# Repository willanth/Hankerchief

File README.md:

# Hankerchief

This is a microcontroller driven signal source, used to extend the operating frequencies of the VK3YNG foxhunt sniffer.

The main components of this system are:
* STM32 Nuleo32 board (I used the L432KC) 
* Silabs Si4464 transciever chip
* ADE-1 mixer
* 3.3VDC boost converter suppled by 2x AA/LR6 batteries

There are provisions for user controls (J8 battery on/off, J11 shift frequency) as well as making use of the IO on the Nucleo module that isn't tied up operating the signal source.  There is a provsion for a bicolor LED, and for external 5V power input through a micro-B USB port.
**_IMPORTANT NOTE_**:  
* There is no battery charging facility through the USB power connector
* There is no USB Data access to the Nucleo32 through the USB power connector
* 3.3V Power is supplied by the Nucleo32 onboard regulator (500mA max) when USB power is connected
* The Nucleo32 is not configured for 5V supply and 3.3V source out of the box, it requires a simple modification (in Nucleo documentation, datasheets folder)

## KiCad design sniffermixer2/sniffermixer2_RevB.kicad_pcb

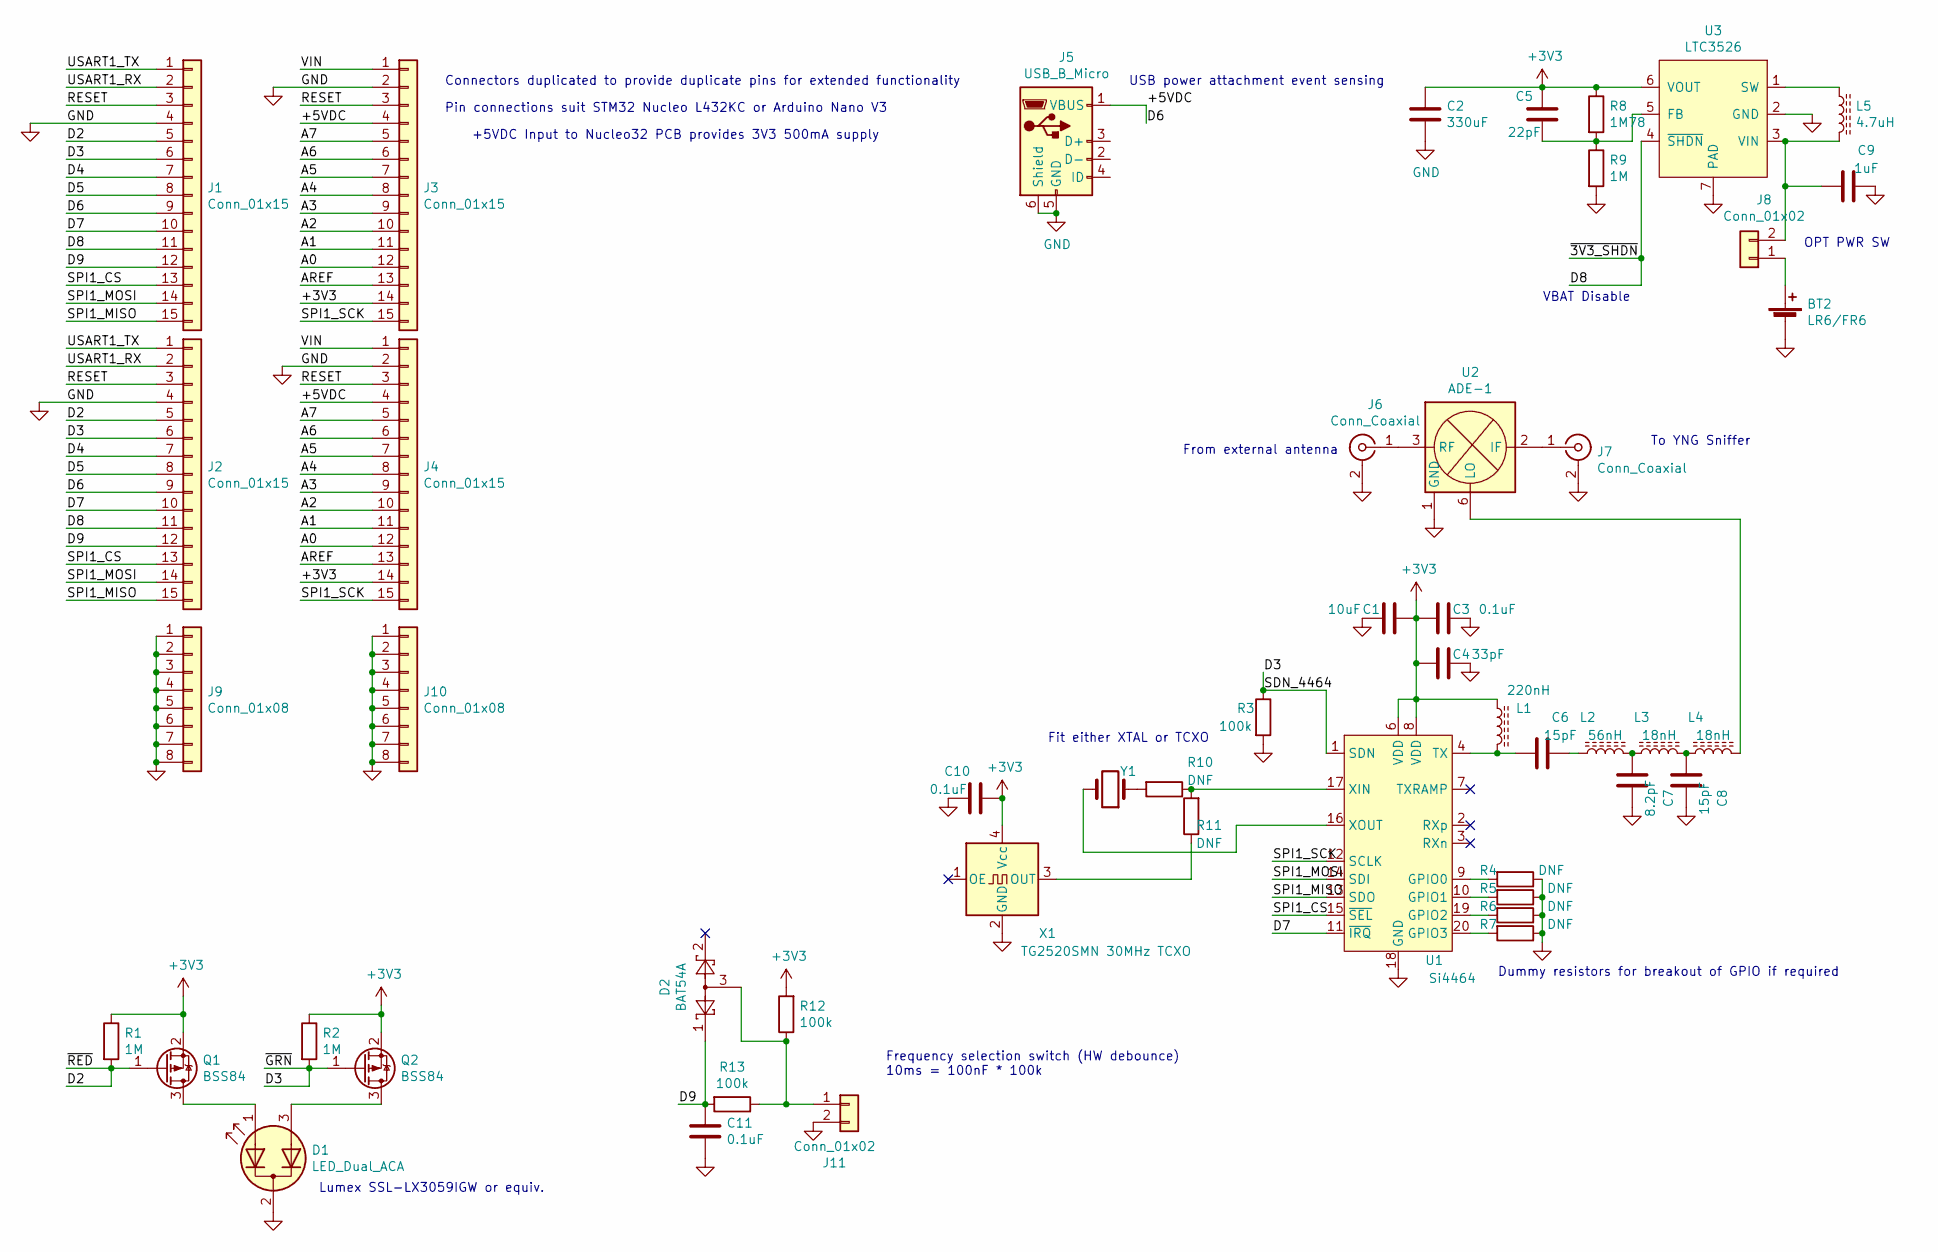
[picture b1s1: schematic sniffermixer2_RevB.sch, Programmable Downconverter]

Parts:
BT2: LR6/FR6; BatteryHolder_Keystone_2462_2xAA
C1: 10uF; C_0603_1608Metric
C2: 330uF; C_0805_2012Metric
C3, C10, C11: 0.1uF; C_0603_1608Metric
C4: 33pF; C_0603_1608Metric
C5: 22pF; C_0603_1608Metric
C6, C8: 15pF; C_0603_1608Metric
C7: 8.2pF; C_0603_1608Metric
C9: 1uF; C_0603_1608Metric
D1: LED_Dual_ACA; LED_D5.0mm-3
D2: BAT54A; SOT-23
J1, J2, J3, J4: Conn_01x15; PinHeader_1x15_P2.54mm_Vertical
J5: USB_B_Micro; USB_Micro-B_Molex_47346-0001
J6, J7: Conn_Coaxial; SMA_Amphenol_901-144_Vertical
J8, J11: Conn_01x02; PinHeader_1x02_P2.54mm_Vertical
J9, J10: Conn_01x08; PinHeader_1x08_P2.54mm_Vertical
L1: 220nH; L_0805_2012Metric_Pad1.15x1.40mm_HandSolder
L2: 56nH; L_0805_2012Metric_Pad1.15x1.40mm_HandSolder
L3, L4: 18nH; L_0805_2012Metric_Pad1.15x1.40mm_HandSolder
L5: 4.7uH; L_0805_2012Metric_Pad1.15x1.40mm_HandSolder
Q1, Q2: BSS84; SOT-23
R1, R2, R9: 1M; R_0603_1608Metric
R3, R12, R13: 100k; R_0603_1608Metric
R4, R5, R6, R7, R10, R11: DNF; R_0603_1608Metric
R8: 1M78; R_0603_1608Metric
U1: Si4464; QFN-20-1EP_4x4mm_P0.5mm_EP2.6x2.6mm
U2: ADE-1; Mini-Circuits_CD542_LandPatternPL-052
U3: LTC3526; DFN-6-1EP_2x2mm_P0.5mm_EP0.61x1.42mm
X1: TG2520SMN 30MHz TCXO; Oscillator_SMD_SeikoEpson_SG210-4Pin_2.5x2.0mm
Y1: Crystal; Crystal_SMD_2520-4Pin_2.5x2.0mm

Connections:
+3V3: C1.1, C2.1, C3.2, C4.2, C5.2, C10.2, J3.14, J4.14, L1.1, Q1.2 (S), Q2.2 (S), R1.1, R2.1, R8.1, R12.2, U1.6 (VDD), U1.8 (VDD), U3.6 (VOUT), X1.4 (Vcc)
/+5VDC: J1.9, J2.9, J3.4, J4.4, J5.1 (VBUS)
/A0: J3.12, J4.12
/A1: J3.11, J4.11
/A2: J3.10, J4.10
/A3: J3.9, J4.9
/A4: J3.8, J4.8
/A5: J3.7, J4.7
/A6: J3.6, J4.6
/A7: J3.5, J4.5
/AREF: J3.13, J4.13
/D2: J1.5, J2.5, Q1.1 (G), R1.2
/D7: J1.10, J2.10, U1.11 (~IRQ)
/D9: C11.1, D2.1, J1.12, J2.12, R13.2
/RESET: J1.3, J2.3, J3.3, J4.3
/SPI1_CS: J1.13, J2.13, U1.15 (~SEL)
/SPI1_MISO: J1.15, J2.15, U1.13 (SDO)
/SPI1_MOSI: J1.14, J2.14, U1.14 (SDI)
/SPI1_SCK: J3.15, J4.15, U1.12 (SCLK)
/USART1_RX: J1.2, J2.2
/USART1_TX: J1.1, J2.1
/VIN: J3.1, J4.1
GND: BT2.2 (-), C1.2, C2.2, C3.1, C4.1, C7.1, C8.1, C9.1, C10.1, C11.2, D1.2 (K), J1.4, J2.4, J3.2, J4.2, J5.5 (GND), J5.6 (Shield), J6.2 (Ext), J7.2 (Ext), J9.1, J9.2, J9.3, J9.4, J9.5, J9.6, J9.7, J9.8, J10.1, J10.2, J10.3, J10.4, J10.5, J10.6, J10.7, J10.8, J11.2, R3.2, R4.1, R5.1, R6.1, R7.1, R9.2, U1.18 (GND), U1.21 (GND), U2.1 (GND), U2.4 (GND), U2.5 (GND), U3.2 (GND), U3.7 (PAD), X1.2 (GND)
unnamed: BT2.1 (+), J8.1
unnamed: C5.1, R8.2, R9.1, U3.5 (FB)
unnamed: C6.1, L2.1
unnamed: C6.2, L1.2, U1.4 (TX)
unnamed: C7.2, L2.2, L3.1
unnamed: C8.2, L3.2, L4.1
unnamed: C9.2, J8.2, L5.2, U3.3 (VIN)
unnamed: D1.1 (A1), Q1.3 (D)
unnamed: D1.3 (A2), Q2.3 (D)
unnamed: D2.3, J11.1, R12.1, R13.1
unnamed: J6.1 (In), U2.3 (RF)
unnamed: J7.1 (In), U2.2 (IF)
unnamed: L4.2, U2.6 (LO)
unnamed: L5.1, U3.1 (SW)
unnamed: R4.2, U1.9 (GPIO0)
unnamed: R5.2, U1.10 (GPIO1)
unnamed: R6.2, U1.19 (GPIO2)
unnamed: R7.2, U1.20 (GPIO3)
unnamed: R10.1, R11.2, U1.17 (XIN)
unnamed: R10.2, Y1.1
unnamed: R11.1, X1.3 (OUT)
unnamed: U1.16 (XOUT), Y1.2

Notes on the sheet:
Connectors duplicated to provide duplicate pins for extended functionality
Pin connections suit STM32 Nucleo L432KC or Arduino Nano V3
Lumex SSL-LX3059IGW or equiv.
To YNG Sniffer
From external antenna
USB power attachment event sensing
VBAT Disable
OPT PWR SW
Dummy resistors for breakout of GPIO if required
Fit either XTAL or TCXO
+5VDC Input to Nucleo32 PCB provides 3V3 500mA supply
Frequency selection switch (HW debounce) 10ms = 100nF * 100k

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
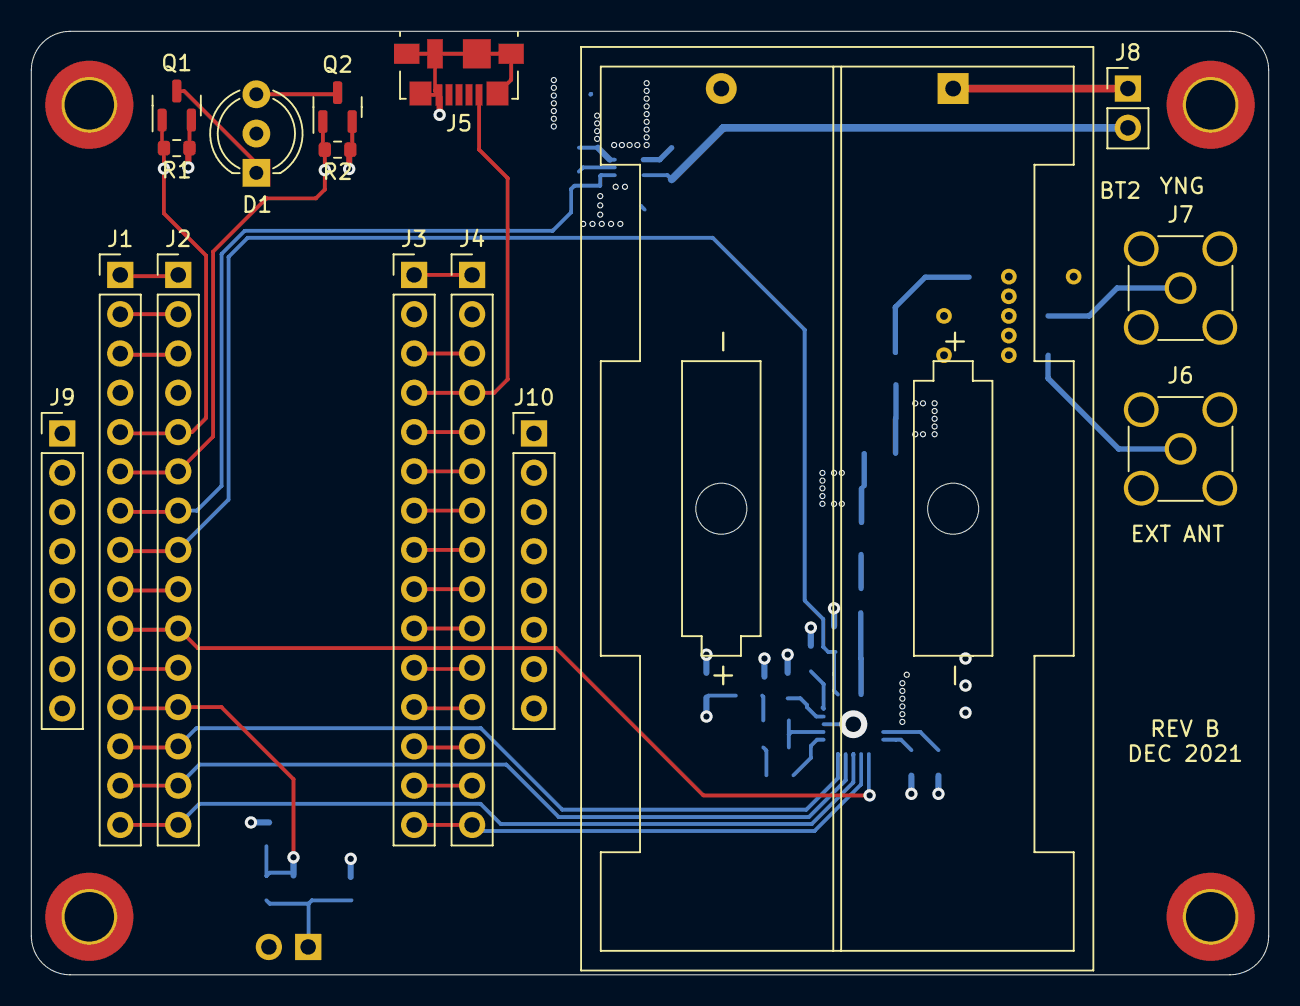
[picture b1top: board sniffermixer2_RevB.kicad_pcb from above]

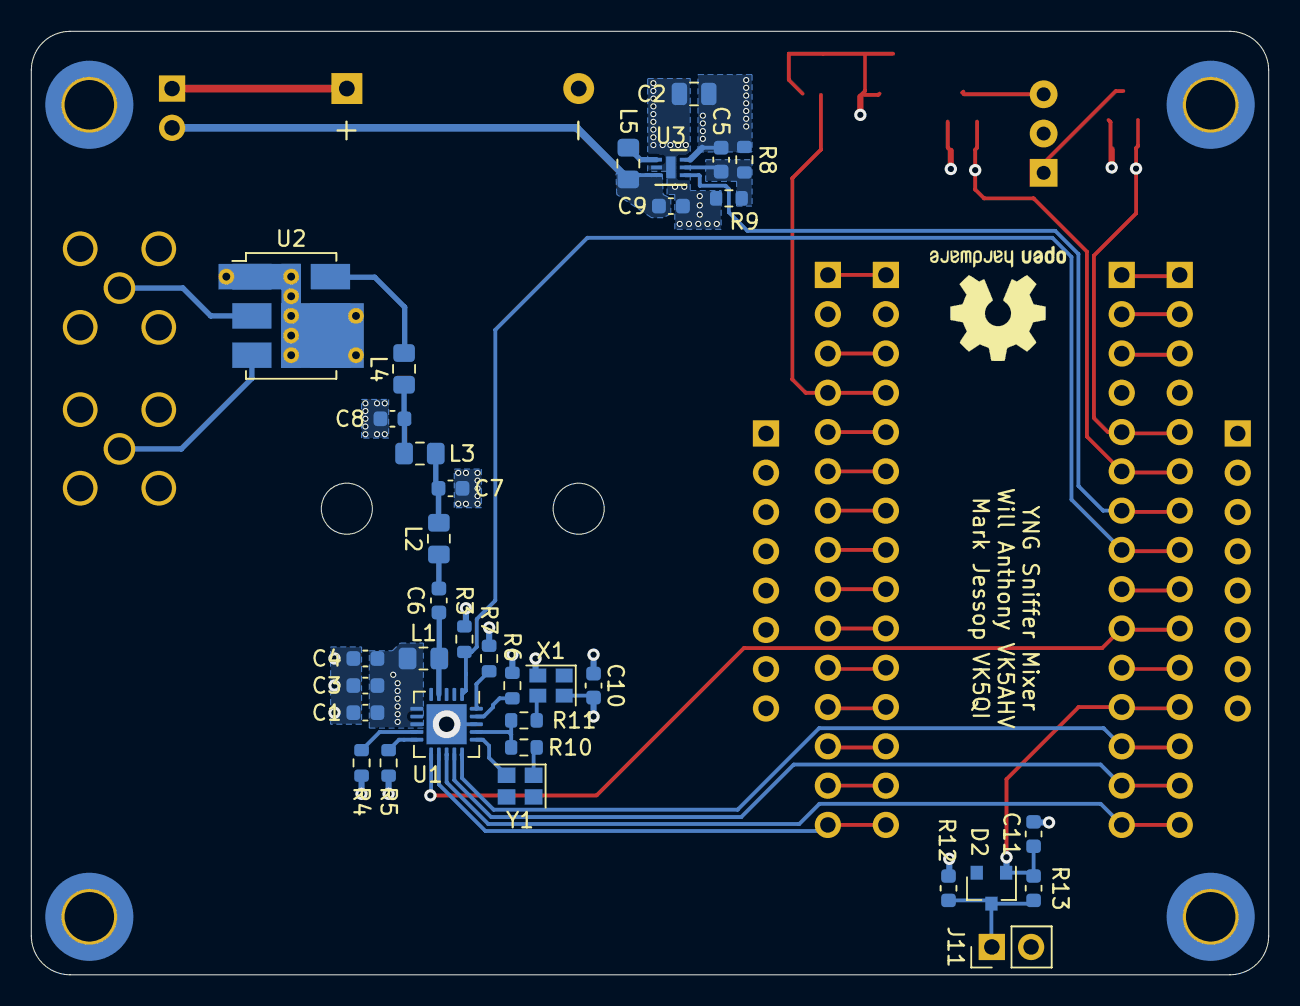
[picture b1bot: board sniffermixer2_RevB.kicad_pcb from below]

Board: 4 copper layers, 80.0 x 61.0 mm, 50 parts (34 on the bottom side), 49 nets.

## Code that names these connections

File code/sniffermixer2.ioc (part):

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PA6.Mode=Full_Duplex_Master
PA15\ (JTDI).GPIOParameters=GPIO_Label
Mcu.UserName=STM32L432KCUx
PA12.GPIOParameters=GPIO_PuPd,GPIO_Label
PA0.GPIO_Label=MCO [High speed clock in]
PB0.GPIO_Label=SHDN_4464
PB6.GPIO_Label=LED_RED
PA15\ (JTDI).Signal=USART2_RX
PC15-OSC32_OUT\ (PC15).Mode=LSE-External-Oscillator
PA2.GPIOParameters=GPIO_Label
RCC.SYSCLKSource=RCC_SYSCLKSOURCE_PLLCLK
PB3\ (JTDO-TRACESWO).Signal=GPIO_Output
PC14-OSC32_IN\ (PC14).Mode=LSE-External-Oscillator
PA14\ (JTCK-SWCLK).Signal=SYS_JTCK-SWCLK
PA15\ (JTDI).Mode=Asynchronous
PA12.Signal=GPIO_Output
PA4.Mode=NSS_Signal_Hard_Output
PB0.PinState=GPIO_PIN_SET
PA14\ (JTCK-SWCLK).GPIOParameters=GPIO_Label
PB1.GPIO_PuPd=GPIO_PULLDOWN
PB1.GPIO_ModeDefaultEXTI=GPIO_MODE_EVT_RISING_FALLING
PB6.Signal=GPIO_Output
PA8.GPIOParameters=GPIO_Label,GPIO_ModeDefaultEXTI
RCC.HSE_VALUE=8000000
PB0.GPIOParameters=PinState,GPIO_PuPd,GPIO_Label
PB1.GPIO_Label=USB_PWR_SENSE
PA0.Mode=HSE-External-Clock-Source-for-LittleOrca
PB7.Signal=GPIO_Output
PA8.Signal=GPXTI8
PB6.GPIOParameters=PinState,GPIO_Label
PA0.Signal=RCC_CK_IN
PB7.PinState=GPIO_PIN_RESET
PB7.GPIO_Label=LED_GRN
Mcu.Package=UFQFPN32
PA6.Signal=SPI1_MISO
PB1.Signal=GPXTI1
PA8.GPIO_ModeDefaultEXTI=GPIO_MODE_IT_RISING_FALLING
PA2.GPIO_Label=VCP_TX
PA13\ (JTMS-SWDIO).Signal=SYS_JTMS-SWDIO
PA12.GPIO_PuPd=GPIO_PULLUP
PA13\ (JTMS-SWDIO).GPIOParameters=GPIO_Label
PB7.GPIO_PuPd=GPIO_NOPULL
PA14\ (JTCK-SWCLK).Mode=Serial_Wire
PA7.Mode=Full_Duplex_Master
PC15-OSC32_OUT\ (PC15).Signal=RCC_OSC32_OUT
PA14\ (JTCK-SWCLK).GPIO_Label=SWCLK
PB3\ (JTDO-TRACESWO).GPIO_Label=LD3 [Green]
boardIOC=true
PA12.GPIO_Label=SHDN_VBAT
PA8.GPIO_Label=SI4464_IRQ
PB7.GPIOParameters=PinState,GPIO_PuPd,GPIO_Label
PA1.Signal=SPI1_SCK
board=NUCLEO-L432KC
PA1.Mode=Full_Duplex_Master
PB3\ (JTDO-TRACESWO).GPIOParameters=GPIO_Label
PA13\ (JTMS-SWDIO).GPIO_Label=SWDIO
PA15\ (JTDI).GPIO_Label=VCP_RX
Mcu.Name=STM32L432K(B-C)Ux
PA2.Signal=USART2_TX
PA13\ (JTMS-SWDIO).Mode=Serial_Wire
PA4.Signal=SPI1_NSS
RCC.SYSCLKFreq_VALUE=32000000
PC14-OSC32_IN\ (PC14).Signal=RCC_OSC32_IN
PB6.PinState=GPIO_PIN_RESET
PA0.GPIOParameters=GPIO_Label
PA2.Mode=Asynchronous
PB0.Signal=GPIO_Output
PB0.GPIO_PuPd=GPIO_PULLDOWN
PB1.GPIOParameters=GPIO_PuPd,GPIO_Label,GPIO_ModeDefaultEXTI
PA7.Signal=SPI1_MOSI

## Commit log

2021-07-05 Project start some basic schematic capture performed
2021-07-05 some minor schematic capture: dupe connectors, tricolor LED, wiring
2021-12-18 Revision B hardware finalized and ready for production
2021-12-18 hardware Revision B is complete and code development beginning
2021-12-18 Update README.md
    added additional information around USB powering of the device
